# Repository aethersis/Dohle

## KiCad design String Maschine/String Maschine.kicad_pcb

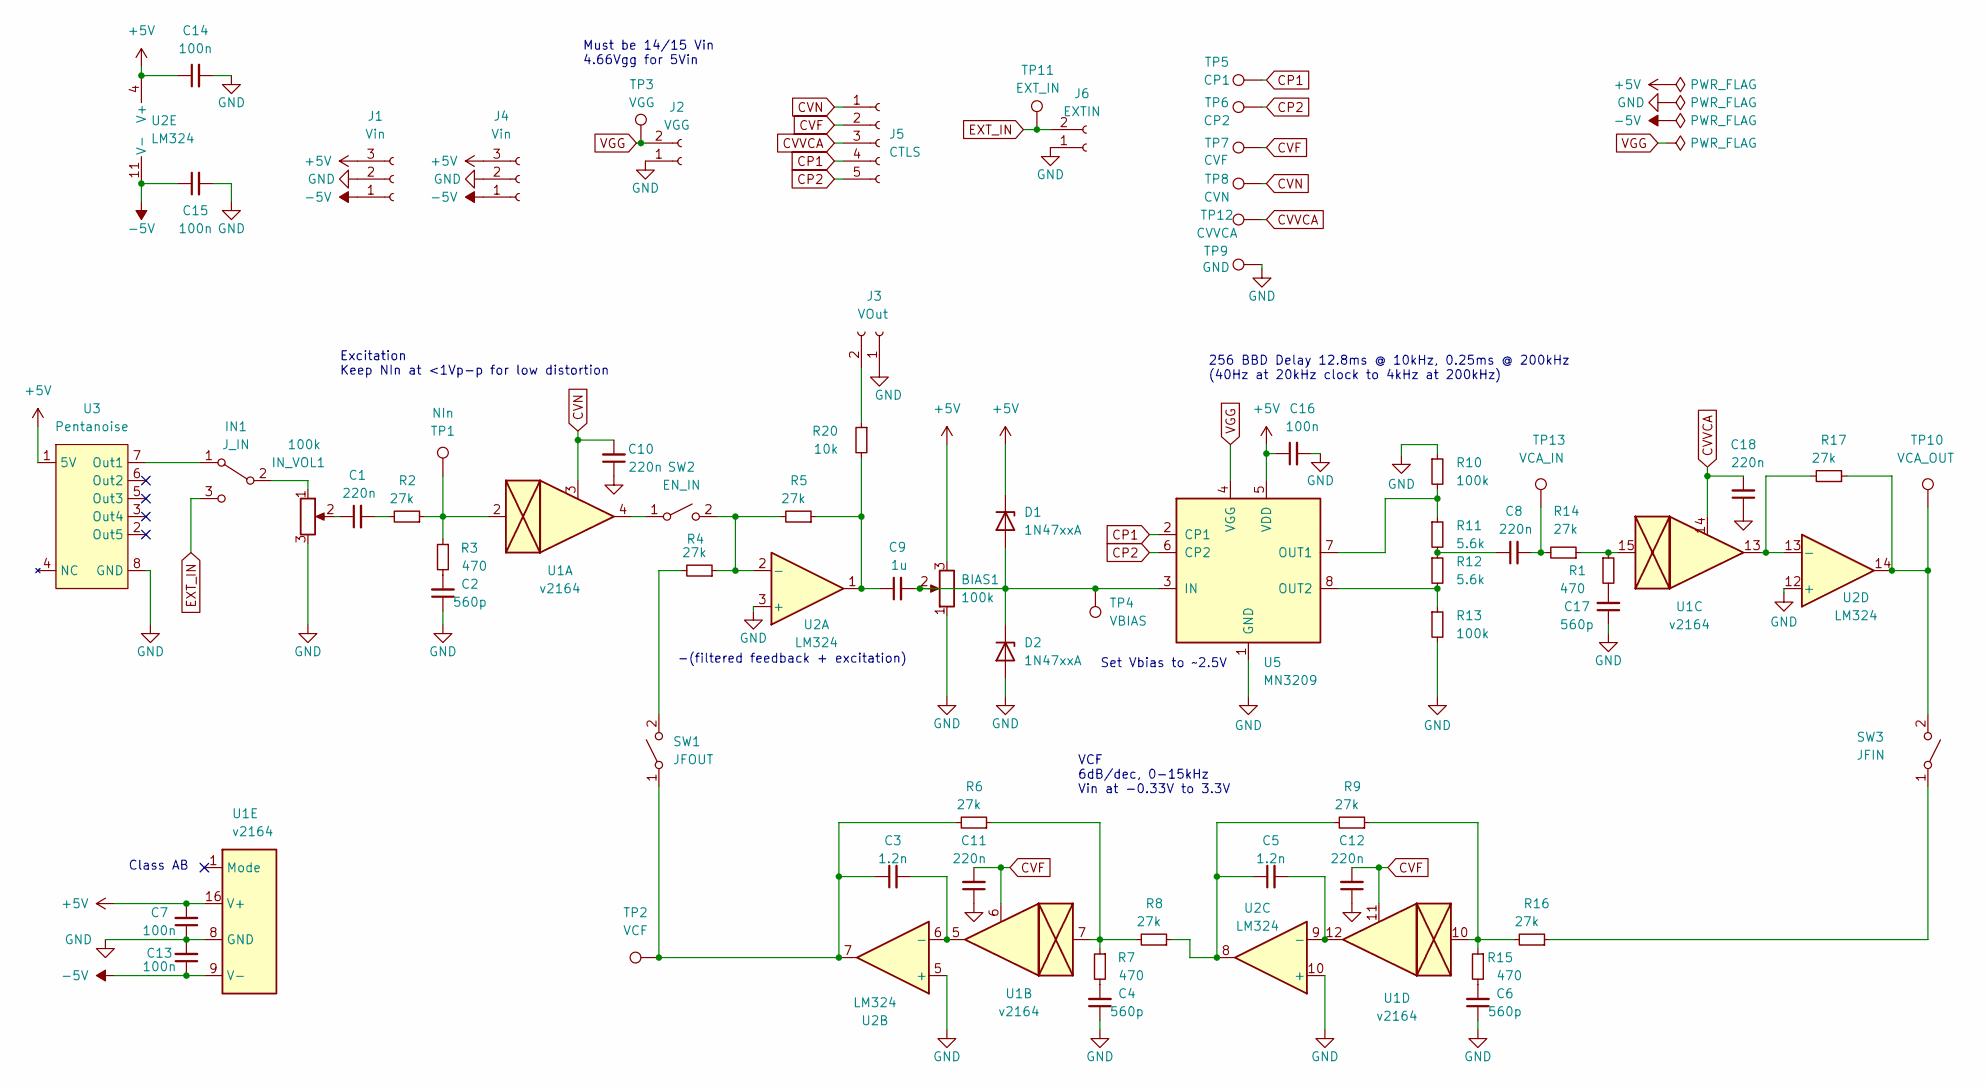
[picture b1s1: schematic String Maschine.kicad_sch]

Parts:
BIAS1: 100k; Potentiometer_Bourns_3266Y_Vertical
C1, C10, C11, C12, C18: 220n; C_Rect_L7.0mm_W3.5mm_P5.00mm
C2, C4, C6, C17: 560p; C_Disc_D5.0mm_W2.5mm_P5.00mm
C3, C5: 1.2n; C_Rect_L7.0mm_W2.5mm_P5.00mm
C7, C13, C14, C15, C16: 100n; C_Rect_L7.0mm_W3.5mm_P5.00mm
C8: 220n; C_Rect_L7.0mm_W4.5mm_P5.00mm
C9: 1u; C_Rect_L7.0mm_W4.5mm_P5.00mm
D1, D2: 1N47xxA; D_DO-41_SOD81_P7.62mm_Horizontal
IN1: J_IN; PinHeader_1x03_P2.54mm_Vertical
IN_VOL1: 100k; Potentiometer_Bourns_3266Y_Vertical
J1, J4: Vin; PinHeader_1x03_P2.54mm_Vertical
J2: VGG; PinHeader_1x02_P2.54mm_Vertical
J3: VOut; PinHeader_1x02_P2.54mm_Vertical
J5: CTLS; PinHeader_1x05_P2.54mm_Vertical
J6: EXTIN; PinHeader_1x02_P2.54mm_Vertical
R1, R3, R7, R15: 470; R_Axial_DIN0207_L6.3mm_D2.5mm_P10.16mm_Horizontal
R2, R4, R5, R6, R8, R9, R14, R16, R17: 27k; R_Axial_DIN0207_L6.3mm_D2.5mm_P10.16mm_Horizontal
R10, R13: 100k; R_Axial_DIN0207_L6.3mm_D2.5mm_P10.16mm_Horizontal
R11, R12: 5.6k; R_Axial_DIN0207_L6.3mm_D2.5mm_P10.16mm_Horizontal
R20: 10k; R_Axial_DIN0207_L6.3mm_D2.5mm_P10.16mm_Horizontal
SW1: JFOUT; PinHeader_1x02_P2.54mm_Vertical
SW2: EN_IN; PinHeader_1x02_P2.54mm_Vertical
SW3: JFIN; PinHeader_1x02_P2.54mm_Vertical
TP1: NIn; TestPoint_Pad_D1.0mm
TP2: VCF; TestPoint_Pad_D1.0mm
TP3: VGG; TestPoint_Pad_D1.0mm
TP4: VBIAS; TestPoint_Pad_D1.0mm
TP5: CP1; TestPoint_Pad_D1.0mm
TP6: CP2; TestPoint_Pad_D1.0mm
TP7: CVF; TestPoint_Pad_D1.0mm
TP8: CVN; TestPoint_Pad_D1.0mm
TP9: GND; TestPoint_Pad_D1.0mm
TP10: VCA_OUT; TestPoint_Pad_D1.0mm
TP11: EXT_IN; TestPoint_Pad_D1.0mm
TP12: CVVCA; TestPoint_Pad_D1.0mm
TP13: VCA_IN; TestPoint_Pad_D1.0mm
U1: v2164; DIP-16_W7.62mm
U2: LM324; DIP-14_W7.62mm
U3: Pentanoise; DIP-8_W7.62mm
U5: MN3209; DIP-8_W7.62mm

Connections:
+5V: BIAS1.3, C7.2, C14.1, C16.1, D1.1 (K), J1.3, J4.3, U1.16 (V+), U2.4 (V+), U3.1 (5V), U5.5 (VDD)
-5V: C13.1, C15.1, J1.1, J4.1, U1.9 (V-), U2.11 (V-)
CP1: J5.4, TP5.1, U5.2 (CP1)
CP2: J5.5, TP6.1, U5.6 (CP2)
CVF: C11.2, C12.2, J5.2, TP7.1, U1.6, U1.11
CVN: C10.2, J5.1, TP8.1, U1.3
CVVCA: C18.2, J5.3, TP12.1, U1.14
EXT_IN: IN1.3 (C), J6.2, TP11.1
GND: BIAS1.1, C2.1, C4.1, C6.1, C7.1, C10.1, C11.1, C12.1, C13.2, C14.2, C15.2, C16.2, C17.1, C18.1, D2.2 (A), IN_VOL1.3, J1.2, J2.1, J3.1, J4.2, J6.1, R10.1, R13.2, TP9.1, U1.8 (GND), U2.3 (+), U2.5 (+), U2.10 (+), U2.12 (+), U3.8 (GND), U5.1 (GND)
unnamed: BIAS1.2, C9.2, D1.2 (A), D2.1 (K), TP4.1, U5.3 (IN)
unnamed: C1.1, IN_VOL1.2
unnamed: C1.2, R2.2
unnamed: C2.2, R3.2
unnamed: C3.1, R6.2, SW1.1 (A), TP2.1, U2.7
unnamed: C3.2, U1.5, U2.6 (-)
unnamed: C4.2, R7.2
unnamed: C5.1, R8.1, R9.2, U2.8
unnamed: C5.2, U1.12, U2.9 (-)
unnamed: C6.2, R15.2
unnamed: C8.1, R11.2, R12.1
unnamed: C8.2, R14.2, TP13.1
unnamed: C9.1, R5.1, R20.2, U2.1
unnamed: C17.2, R1.2
unnamed: IN1.1 (A), U3.7 (Out1)
unnamed: IN1.2 (B), IN_VOL1.1
unnamed: J3.2, R20.1
unnamed: R1.1, R14.1, U1.15
unnamed: R2.1, R3.1, TP1.1, U1.2
unnamed: R4.1, R5.2, SW2.2 (B), U2.2 (-)
unnamed: R4.2, SW1.2 (B)
unnamed: R6.1, R7.1, R8.2, U1.7
unnamed: R10.2, R11.1, U5.7 (OUT1)
unnamed: R12.2, R13.1, U5.8 (OUT2)
unnamed: R9.1, R15.1, R16.2, U1.10
unnamed: R16.1, SW3.1 (A)
unnamed: R17.1, SW3.2 (B), TP10.1, U2.14
unnamed: R17.2, U1.13, U2.13 (-)
unnamed: SW2.1 (A), U1.4
VGG: J2.2, TP3.1, U5.4 (VGG)

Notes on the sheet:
Must be 14/15 Vin 4.66Vgg for 5Vin
Set Vbias to ~2.5V
Excitation Keep NIn at <1Vp-p for low distortion
256 BBD Delay 12.8ms @ 10kHz, 0.25ms @ 200kHz (40Hz at 20kHz clock to 4kHz at 200kHz)
VCF 6dB/dec, 0-15kHz Vin at -0.33V to 3.3V
-(filtered feedback + excitation)
Class AB

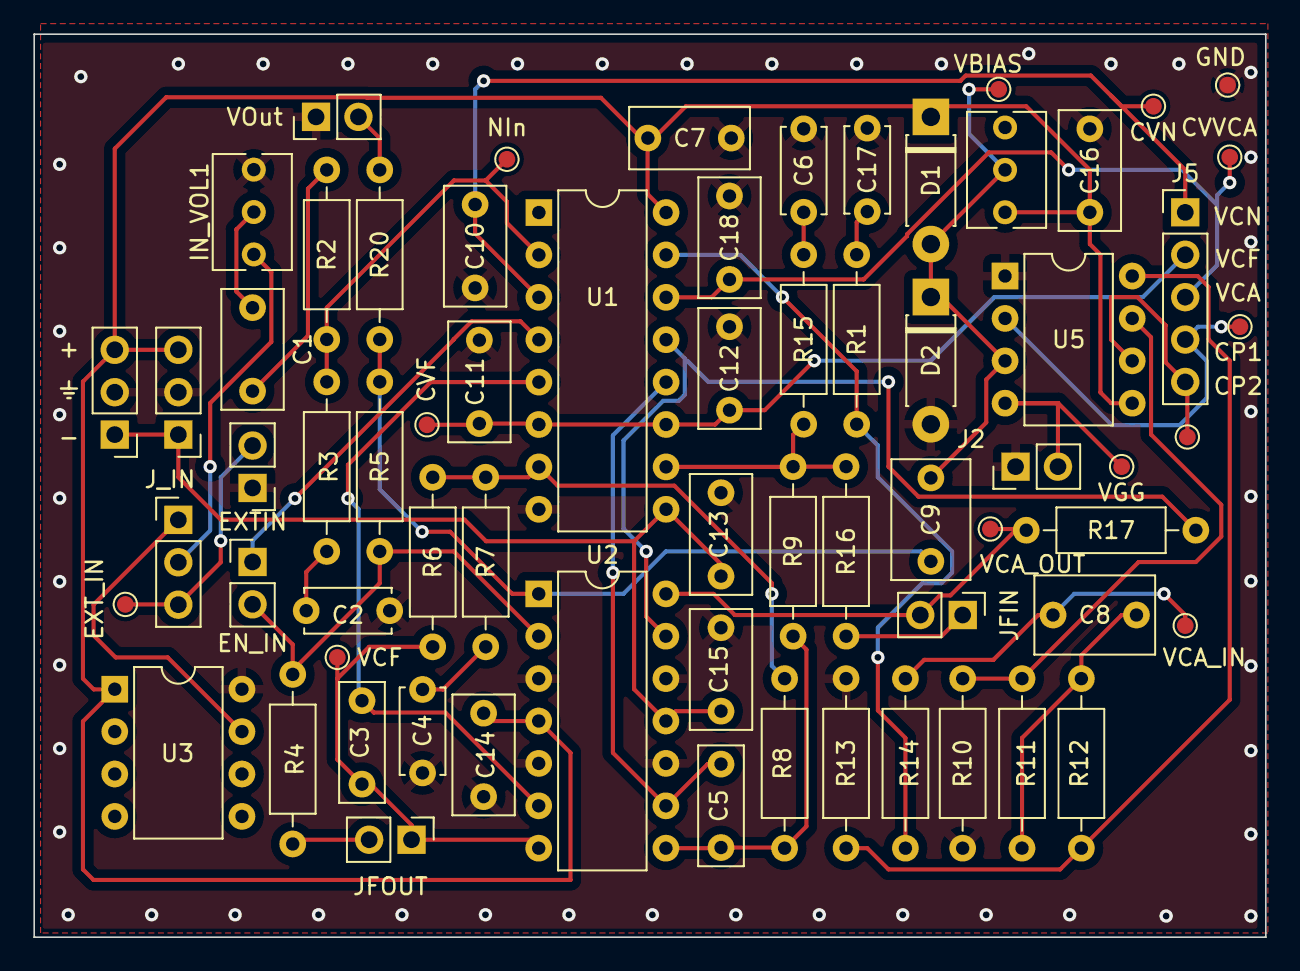
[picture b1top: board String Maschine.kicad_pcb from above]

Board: 2 copper layers, 73.8 x 54.1 mm, 67 parts (0 on the bottom side), 39 nets.

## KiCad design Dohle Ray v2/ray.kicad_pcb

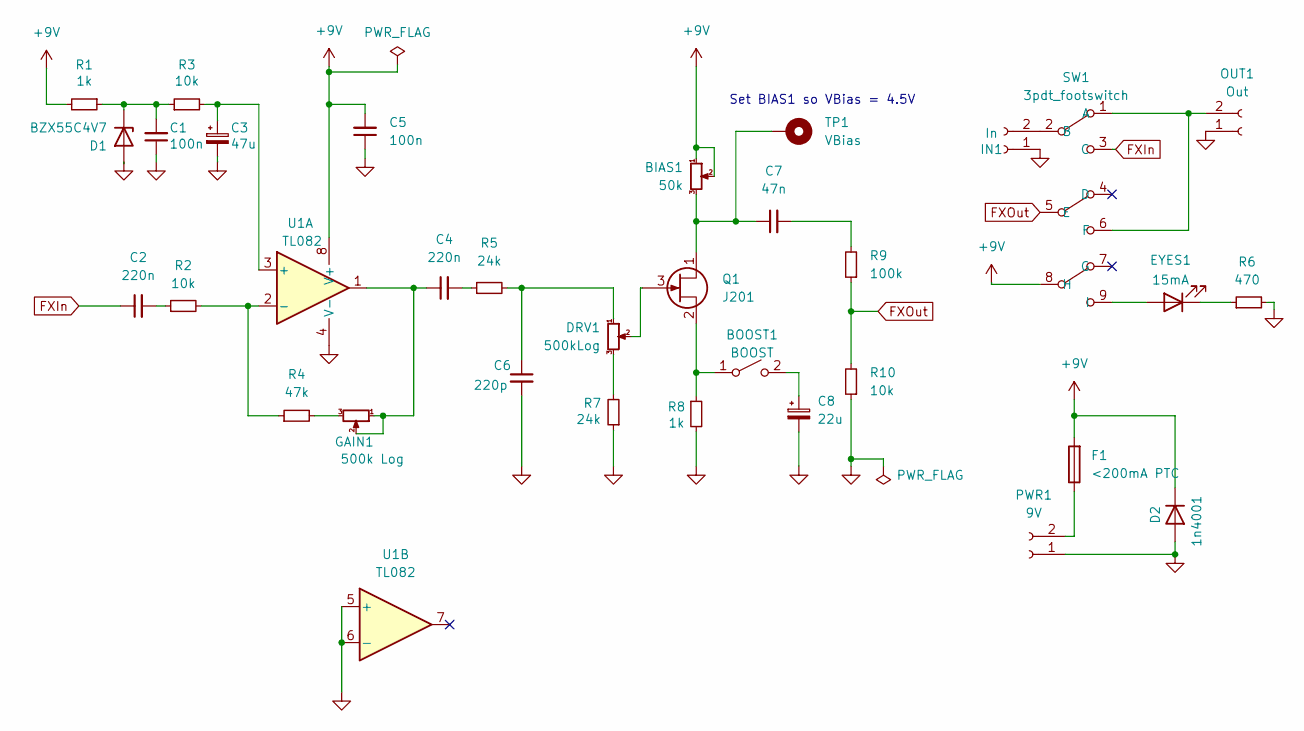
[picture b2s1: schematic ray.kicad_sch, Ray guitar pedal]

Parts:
BIAS1: 50k; Potentiometer_Bourns_3299W_Vertical
BOOST1: BOOST; JST_PH_B2B-PH-K_1x02_P2.00mm_Vertical
C1, C5: 100n; C_Rect_L7.0mm_W4.5mm_P5.00mm
C2, C4: 220n; C_Rect_L7.0mm_W4.5mm_P5.00mm
C3: 47u; CP_Radial_D5.0mm_P2.00mm
C6: 220p; C_Rect_L7.0mm_W2.0mm_P5.00mm
C7: 47n; C_Disc_D5.0mm_W2.5mm_P5.00mm
C8: 22u; CP_Radial_D5.0mm_P2.50mm
D1: BZX55C4V7; D_DO-35_SOD27_P7.62mm_Horizontal
D2: 1n4001; D_DO-15_P12.70mm_Horizontal
DRV1: 500kLog; JST_PH_B3B-PH-K_1x03_P2.00mm_Vertical
EYES1: 15mA; JST_PH_B2B-PH-K_1x02_P2.00mm_Vertical
F1: <200mA PTC; C_Rect_L7.0mm_W4.5mm_P5.00mm
GAIN1: 500k Log; JST_PH_B3B-PH-K_1x03_P2.00mm_Vertical
IN1: In; JST_PH_B2B-PH-K_1x02_P2.00mm_Vertical
OUT1: Out; JST_PH_B2B-PH-K_1x02_P2.00mm_Vertical
PWR1: 9V; JST_PH_B2B-PH-K_1x02_P2.00mm_Vertical
Q1: J201; SOT-23_Handsoldering
R1, R8: 1k; R_Axial_DIN0207_L6.3mm_D2.5mm_P10.16mm_Horizontal
R2, R3, R10: 10k; R_Axial_DIN0207_L6.3mm_D2.5mm_P10.16mm_Horizontal
R4: 47k; R_Axial_DIN0207_L6.3mm_D2.5mm_P10.16mm_Horizontal
R5, R7: 24k; R_Axial_DIN0207_L6.3mm_D2.5mm_P10.16mm_Horizontal
R6: 470; R_Axial_DIN0207_L6.3mm_D2.5mm_P10.16mm_Horizontal
R9: 100k; R_Axial_DIN0207_L6.3mm_D2.5mm_P10.16mm_Horizontal
SW1: 3pdt_footswitch
TP1: VBias; TestPoint_THTPad_1.5x1.5mm_Drill0.7mm
U1: TL082; DIP-8_W7.62mm_Socket_LongPads

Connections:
+9V: BIAS1.1, BIAS1.2, C5.2, D2.1 (K), F1.2, R1.2, SW1.8 (H), U1.8 (V+)
FXIn: C2.1, SW1.3 (C)
FXOut: R9.1, R10.2, SW1.5 (E)
GND: C1.1, C3.2, C5.1, C6.2, C8.2, D1.2 (A), D2.2 (A), IN1.1, OUT1.1, PWR1.1, R6.2, R7.1, R8.2, R10.1, U1.4 (V-), U1.5 (+), U1.6 (-)
unnamed 4: BIAS1.3, C7.1, Q1.1 (D), TP1.1; also elsewhere on the board
unnamed: BOOST1.1 (A), Q1.2 (S), R8.1
unnamed: BOOST1.2 (B), C8.1
unnamed: C1.2, D1.1 (K), R1.1, R3.1
unnamed: C2.2, R2.1
unnamed: C3.1, R3.2, U1.3 (+)
unnamed: C4.1, GAIN1.1, GAIN1.2, U1.1
unnamed: C4.2, R5.1
unnamed: C6.1, DRV1.1, R5.2
unnamed: C7.2, R9.2
unnamed: DRV1.2, Q1.3 (G)
unnamed: DRV1.3, R7.2
unnamed: EYES1.1 (K), R6.1
unnamed: EYES1.2 (A), SW1.9 (I)
unnamed: F1.1, PWR1.2
unnamed: GAIN1.3, R4.2
unnamed: IN1.2, SW1.2 (B)
unnamed: OUT1.2, SW1.1 (A), SW1.6 (F)
unnamed: R2.2, R4.1, U1.2 (-)

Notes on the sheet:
Set BIAS1 so VBias = 4.5V

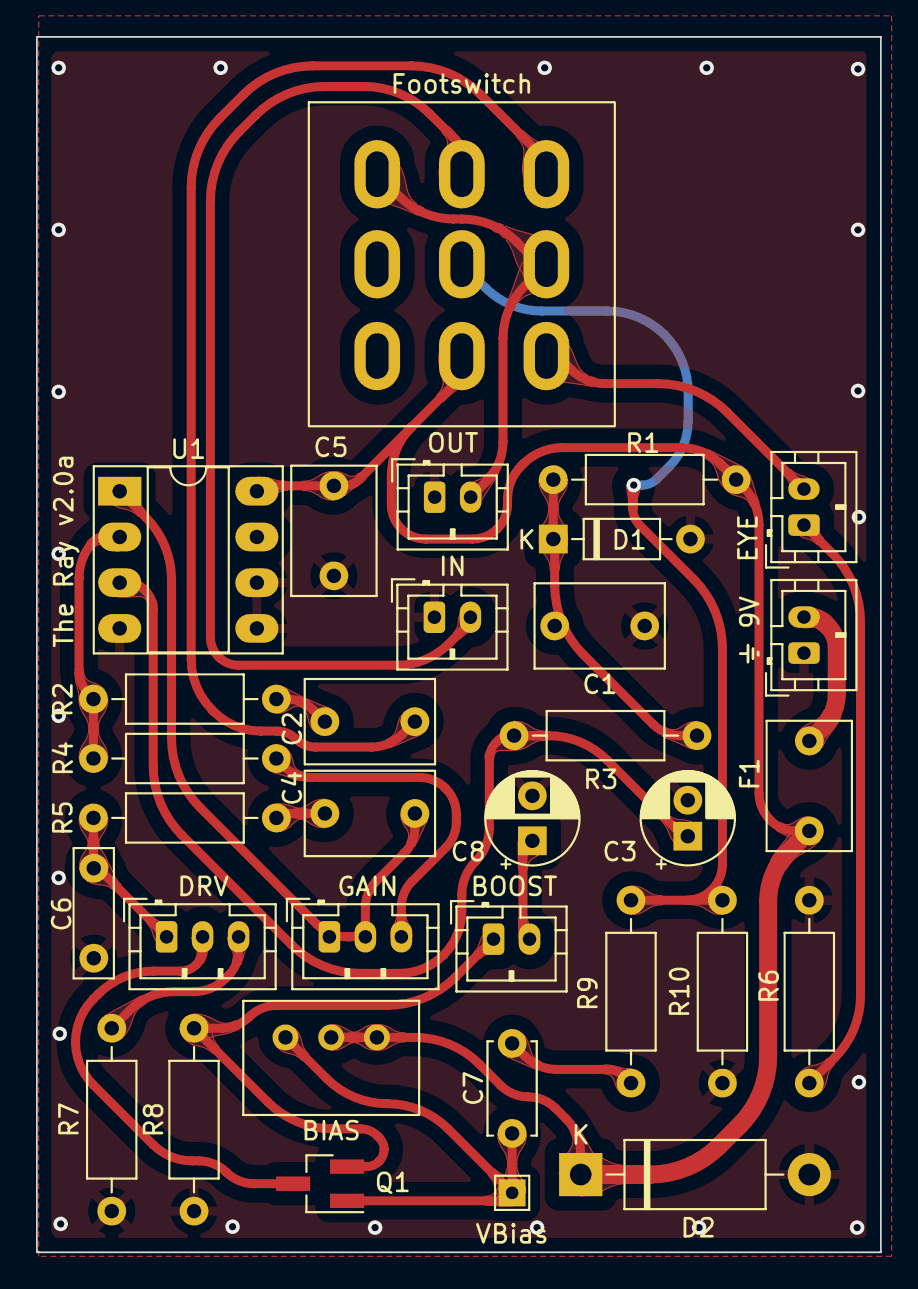
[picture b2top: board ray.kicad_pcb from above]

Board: 2 copper layers, 46.9 x 67.5 mm, 33 parts (0 on the bottom side), 23 nets.

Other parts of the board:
VBias: VBias; TestPoint_THTPad_1.5x1.5mm_Drill0.7mm

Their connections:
unnamed 4: VBias.1; also elsewhere on the board

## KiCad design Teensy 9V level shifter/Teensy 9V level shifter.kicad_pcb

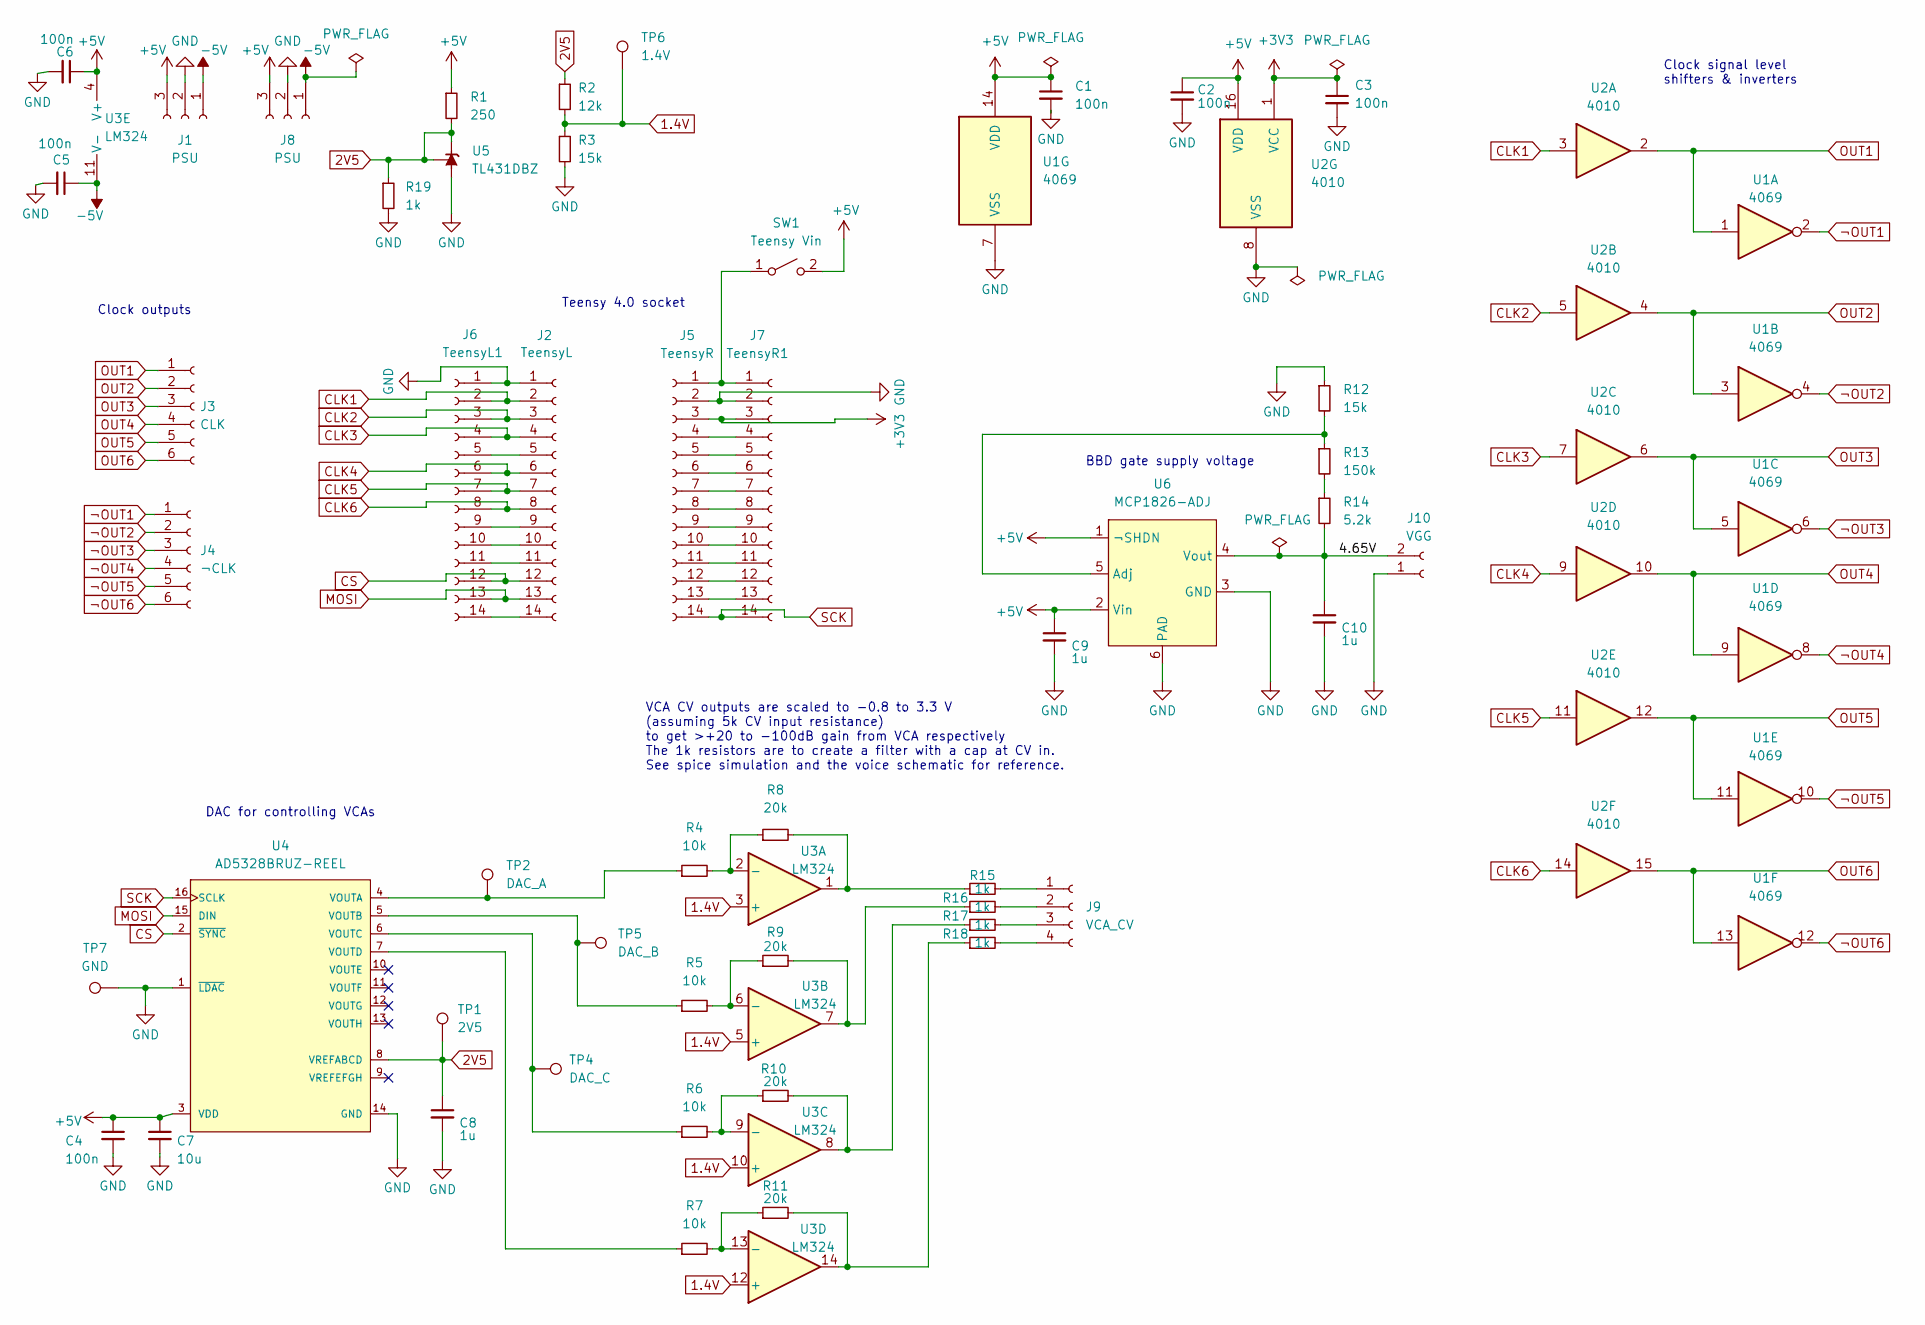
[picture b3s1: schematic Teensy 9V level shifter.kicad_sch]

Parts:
C1, C2, C3: 100n; C_Rect_L7.0mm_W3.5mm_P5.00mm
C4, C5, C6: 100n; C_0603_1608Metric_Pad1.08x0.95mm_HandSolder
C7: 10u; C_0805_2012Metric_Pad1.18x1.45mm_HandSolder
C8, C9, C10: 1u; C_0603_1608Metric_Pad1.08x0.95mm_HandSolder
J1, J8: PSU; PinHeader_1x03_P2.54mm_Vertical
J2: TeensyL; PinHeader_1x14_P2.54mm_Vertical
J3: CLK; PinHeader_1x06_P2.54mm_Vertical
J4: ¬CLK; PinHeader_1x06_P2.54mm_Vertical
J5: TeensyR; PinHeader_1x14_P2.54mm_Vertical
J6: TeensyL1; PinHeader_1x14_P2.54mm_Vertical
J7: TeensyR1; PinHeader_1x14_P2.54mm_Vertical
J9: VCA_CV; PinHeader_1x04_P2.54mm_Vertical
J10: VGG; PinHeader_1x02_P2.54mm_Vertical
R1: 250; R_0603_1608Metric_Pad0.98x0.95mm_HandSolder
R2: 12k; R_0603_1608Metric_Pad0.98x0.95mm_HandSolder
R3, R12: 15k; R_0603_1608Metric_Pad0.98x0.95mm_HandSolder
R4, R5, R6, R7: 10k; R_0603_1608Metric_Pad0.98x0.95mm_HandSolder
R8, R9, R10, R11: 20k; R_0603_1608Metric_Pad0.98x0.95mm_HandSolder
R13: 150k; R_0603_1608Metric_Pad0.98x0.95mm_HandSolder
R14: 5.2k; R_0603_1608Metric_Pad0.98x0.95mm_HandSolder
R15, R16, R17, R18, R19: 1k; R_0603_1608Metric_Pad0.98x0.95mm_HandSolder
SW1: Teensy Vin; PinHeader_1x02_P2.54mm_Vertical
TP1: 2V5; TestPoint_Pad_D1.0mm
TP2: DAC_A; TestPoint_Pad_D1.0mm
TP4: DAC_C; TestPoint_Pad_D1.0mm
TP5: DAC_B; TestPoint_Pad_D1.0mm
TP6: 1.4V; TestPoint_Pad_D1.0mm
TP7: GND; TestPoint_Pad_3.0x3.0mm
U1: 4069; DIP-14_W7.62mm
U2: 4010; DIP-16_W7.62mm
U3: LM324; SO-14_3.9x8.65mm_P1.27mm
U4: AD5328BRUZ-REEL; TSSOP-16_4.4x5mm_P0.65mm
U5: TL431DBZ; SOT-23
U6: MCP1826-ADJ; SOT-223-6

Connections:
1.4V: R2.2, R3.1, TP6.1, U3.3 (+), U3.5 (+), U3.10 (+), U3.12 (+)
2V5: C8.1, R1.2, R2.1, R19.1, TP1.1, U4.8 (VREFABCD), U5.1 (K), U5.2 (REF)
+3V3: C3.1, J5.3, J7.3, U2.1 (VCC)
+5V: C1.1, C2.1, C4.1, C6.1, C7.1, C9.1, J1.3, J8.3, R1.1, SW1.2 (B), U1.14 (VDD), U2.16 (VDD), U3.4 (V+), U4.3 (VDD), U6.1 (¬SHDN), U6.2 (Vin)
-5V: C5.1, J1.1, J8.1, U3.11 (V-)
/4.65V: C10.1, J10.2, R14.2, U6.4 (Vout)
CLK1: J2.2, J6.2, U2.3
CLK2: J2.3, J6.3, U2.5
CLK3: J2.4, J6.4, U2.7
CLK4: J2.6, J6.6, U2.9
CLK5: J2.7, J6.7, U2.11
CLK6: J2.8, J6.8, U2.14
CS: J2.12, J6.12, U4.2 (~SYNC)
GND: C1.2, C2.2, C3.2, C4.2, C5.2, C6.2, C7.2, C8.2, C9.2, C10.2, J1.2, J2.1, J5.2, J6.1, J7.2, J8.2, J10.1, R3.2, R12.1, R19.2, TP7.1, U1.7 (VSS), U2.8 (VSS), U4.1 (~LDAC), U4.14 (GND), U5.3 (A), U6.3 (GND), U6.6 (PAD)
MOSI: J2.13, J6.13, U4.15 (DIN)
unnamed: J2.5, J6.5
unnamed: J2.9, J6.9
unnamed: J2.10, J6.10
unnamed: J2.11, J6.11
unnamed: J2.14, J6.14
unnamed: J5.1, J7.1, SW1.1 (A)
unnamed: J5.4, J7.4
unnamed: J5.5, J7.5
unnamed: J5.6, J7.6
unnamed: J5.7, J7.7
unnamed: J5.8, J7.8
unnamed: J5.9, J7.9
unnamed: J5.10, J7.10
unnamed: J5.11, J7.11
unnamed: J5.12, J7.12
unnamed: J5.13, J7.13
unnamed: J9.1, R15.2
unnamed: J9.2, R16.2
unnamed: J9.3, R17.2
unnamed: J9.4, R18.2
unnamed: R4.1, TP2.1, U4.4 (VOUTA)
unnamed: R5.1, TP5.1, U4.5 (VOUTB)
unnamed: R5.2, R9.1, U3.6 (-)
unnamed: R7.1, U4.7 (VOUTD)
unnamed: R8.2, R15.1, U3.1
unnamed: R6.2, R10.1, U3.9 (-)
unnamed: R10.2, R17.1, U3.8
unnamed: R7.2, R11.1, U3.13 (-)
unnamed: R12.2, R13.1, U6.5 (Adj)
unnamed: R13.2, R14.1
unnamed: R6.1, TP4.1, U4.6 (VOUTC)
unnamed: R4.2, R8.1, U3.2 (-)
unnamed: R9.2, R16.1, U3.7
unnamed: R11.2, R18.1, U3.14
OUT1: J3.1, U1.1, U2.2
OUT2: J3.2, U1.3, U2.4
OUT3: J3.3, U1.5, U2.6
OUT4: J3.4, U1.9, U2.10
OUT5: J3.5, U1.11, U2.12
OUT6: J3.6, U1.13, U2.15
SCK: J5.14, J7.14, U4.16 (SCLK)
¬OUT1: J4.1, U1.2
¬OUT2: J4.2, U1.4
¬OUT3: J4.3, U1.6
¬OUT4: J4.4, U1.8
¬OUT5: J4.5, U1.10
¬OUT6: J4.6, U1.12

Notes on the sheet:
Clock outputs
BBD gate supply voltage
Clock signal level shifters & inverters
DAC for controlling VCAs
VCA CV outputs are scaled to -0.8 to 3.3 V (assuming 5k CV input resistance) to get >+20 to -100dB gain from VCA respectively The 1k resistors are to create a filter with a cap at CV in. See spice simulation and the voice schematic for reference.
Teensy 4.0 socket

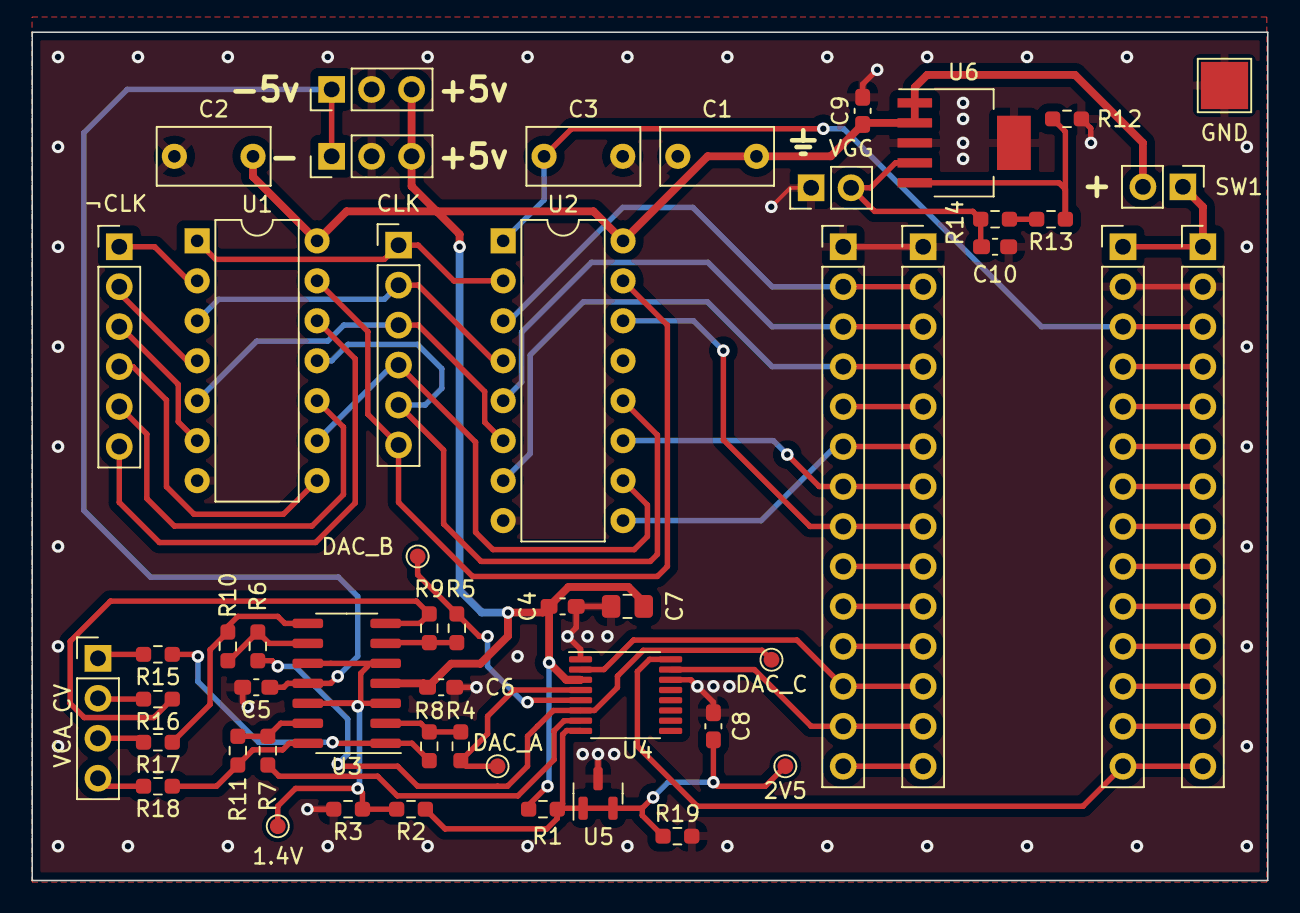
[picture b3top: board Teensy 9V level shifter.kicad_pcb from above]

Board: 2 copper layers, 78.5 x 53.9 mm, 52 parts (0 on the bottom side), 62 nets.

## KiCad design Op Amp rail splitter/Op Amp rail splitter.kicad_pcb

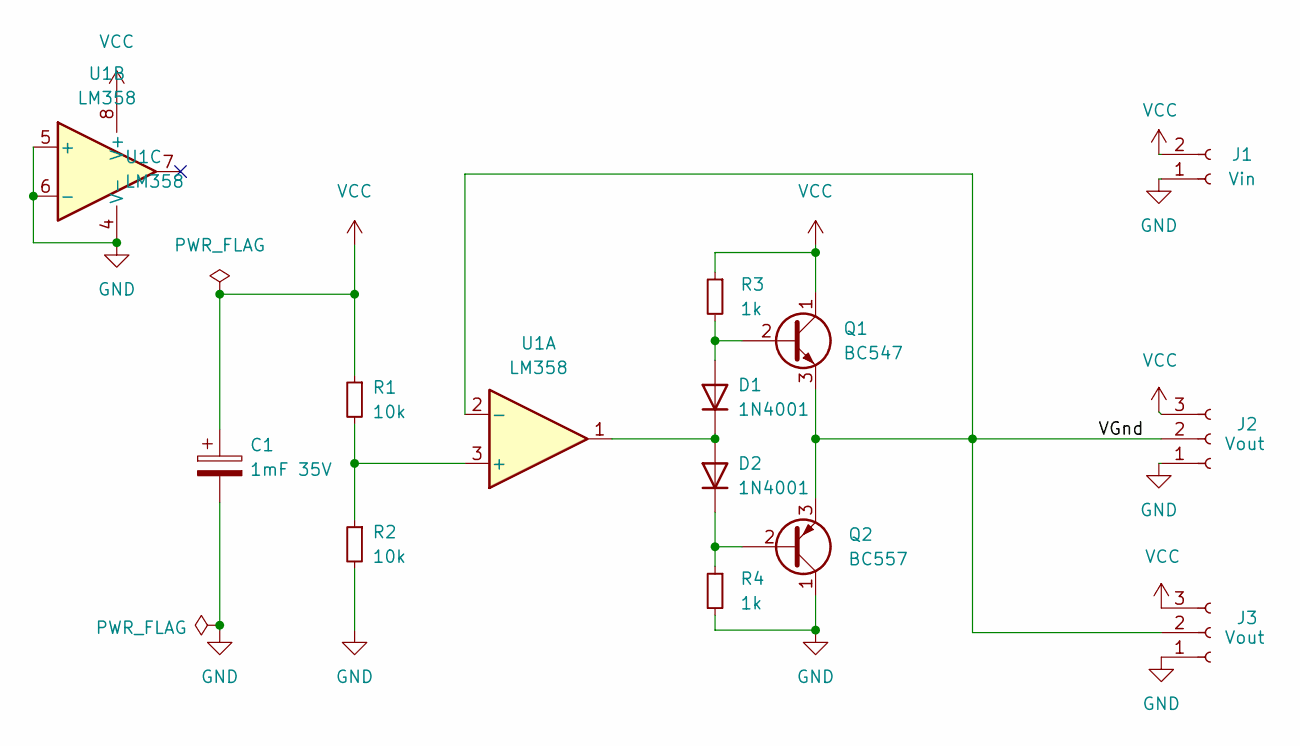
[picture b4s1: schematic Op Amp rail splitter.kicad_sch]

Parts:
C1: 1mF 35V; CP_Radial_D12.5mm_P5.00mm
D1, D2: 1N4001; D_DO-41_SOD81_P10.16mm_Horizontal
J1: Vin; PinHeader_1x02_P2.54mm_Vertical
J2, J3: Vout; PinHeader_1x03_P2.54mm_Vertical
Q1: BC547; TO-92_Inline
Q2: BC557; TO-92_Inline
R1, R2: 10k; R_Axial_DIN0207_L6.3mm_D2.5mm_P10.16mm_Horizontal
R3, R4: 1k; R_Axial_DIN0207_L6.3mm_D2.5mm_P10.16mm_Horizontal
U1: LM358; DIP-8_W7.62mm

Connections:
/VGnd: J2.2, J3.2, Q1.3 (E), Q2.3 (E), U1.2 (-)
GND: C1.2, J1.1, J2.1, J3.1, Q2.1 (C), R2.2, R4.2, U1.4 (V-), U1.5 (+), U1.6 (-)
unnamed: D1.1 (K), D2.2 (A), U1.1
unnamed: D1.2 (A), Q1.2 (B), R3.2
unnamed: D2.1 (K), Q2.2 (B), R4.1
unnamed: R1.2, R2.1, U1.3 (+)
VCC: C1.1, J1.2, J2.3, J3.3, Q1.1 (C), R1.1, R3.1, U1.8 (V+)

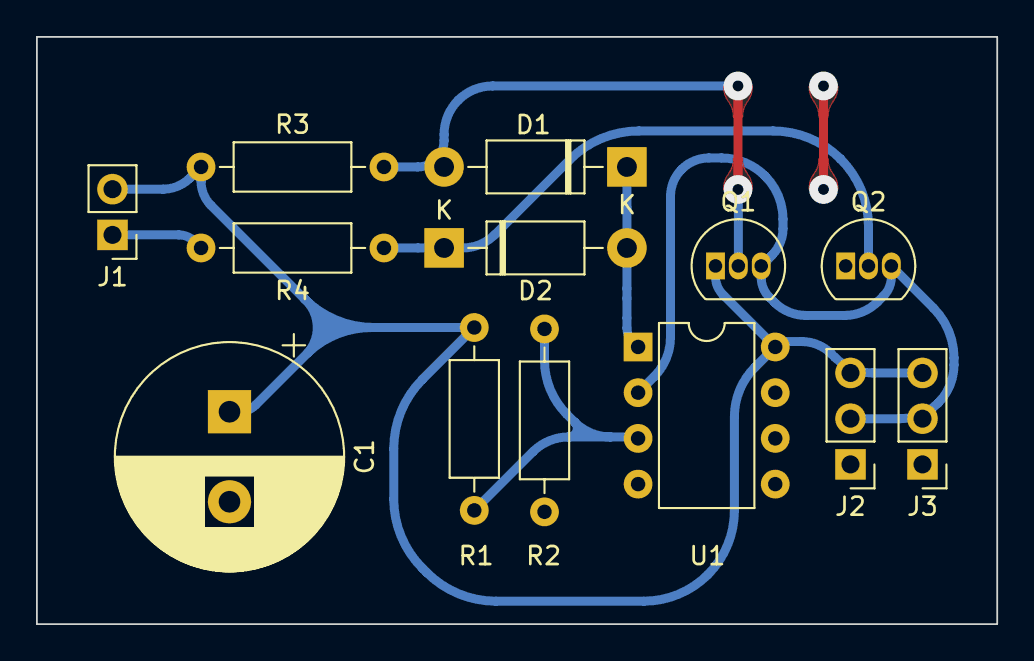
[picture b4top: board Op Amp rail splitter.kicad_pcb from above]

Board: 2 copper layers, 53.4 x 32.6 mm, 13 parts (0 on the bottom side), 7 nets.

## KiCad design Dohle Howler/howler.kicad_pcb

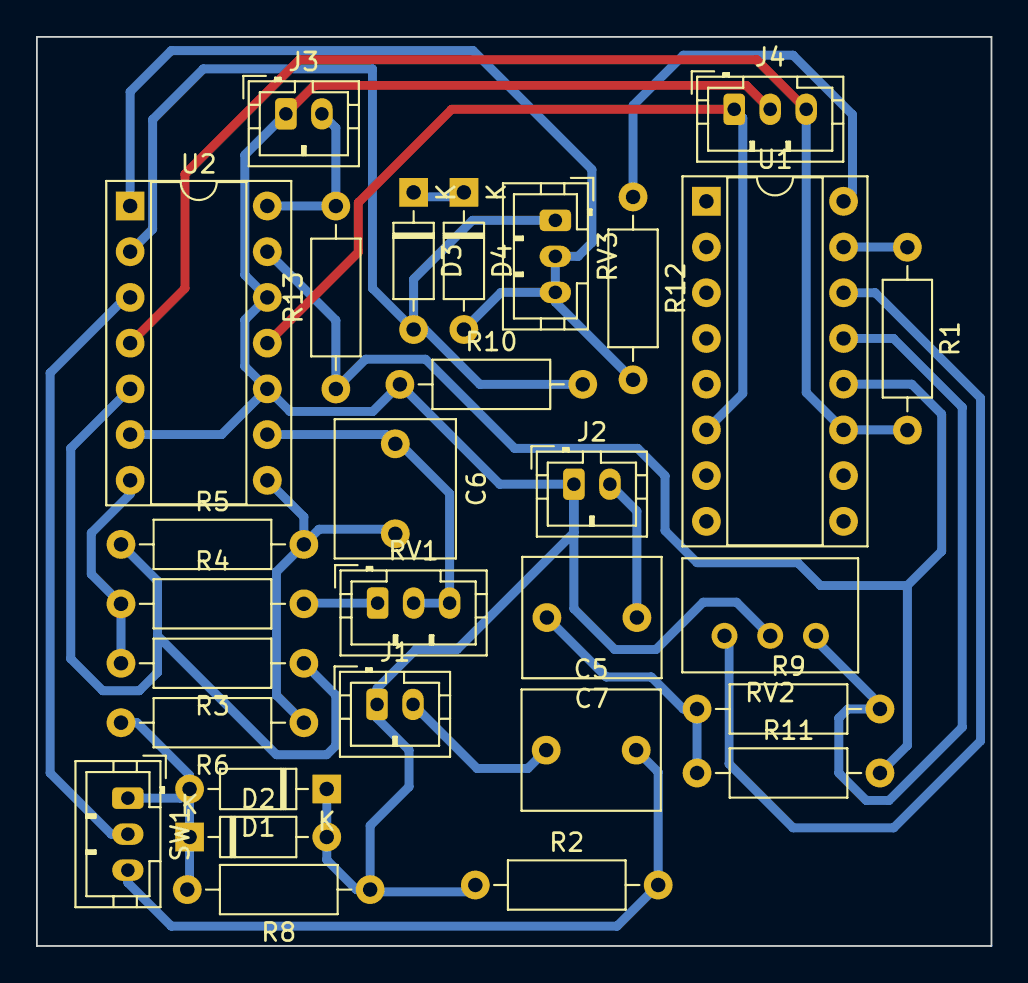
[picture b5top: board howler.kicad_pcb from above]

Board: 2 copper layers, 53.0 x 50.5 mm, 29 parts (0 on the bottom side), 23 nets.

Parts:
C5, C6, C7: 1u; C_Rect_L7.5mm_W6.5mm_P5.00mm
D1, D2: 1n4148; D_DO-35_SOD27_P7.62mm_Horizontal
D3, D4: 4v7; D_DO-35_SOD27_P7.62mm_Horizontal
J1: MOD_IN; JST_PH_B2B-PH-K_1x02_P2.00mm_Vertical
J2: IN; JST_PH_B2B-PH-K_1x02_P2.00mm_Vertical
J3: OUT; JST_PH_B2B-PH-K_1x02_P2.00mm_Vertical
J4: PWR; JST_PH_B3B-PH-K_1x03_P2.00mm_Vertical
R1, R3, R4, R5, R8, R9, R11: 10k; R_Axial_DIN0207_L6.3mm_D2.5mm_P10.16mm_Horizontal
R2: 470k; R_Axial_DIN0207_L6.3mm_D2.5mm_P10.16mm_Horizontal
R6: 100k; R_Axial_DIN0207_L6.3mm_D2.5mm_P10.16mm_Horizontal
R10: 4k7; R_Axial_DIN0207_L6.3mm_D2.5mm_P10.16mm_Horizontal
R12: 15k; R_Axial_DIN0207_L6.3mm_D2.5mm_P10.16mm_Horizontal
R13: 24k; R_Axial_DIN0207_L6.3mm_D2.5mm_P10.16mm_Horizontal
RV1: 500k log; JST_PH_B3B-PH-K_1x03_P2.00mm_Vertical
RV2: 2k; Potentiometer_Bourns_3299W_Vertical
RV3: 50k; JST_PH_B3B-PH-K_1x03_P2.00mm_Vertical
SW1: SW_SPDT; JST_PH_B3B-PH-K_1x03_P2.00mm_Vertical
U1: LM13700; DIP-16_W7.62mm_Socket
U2: LM324; DIP-14_W7.62mm_Socket

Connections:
+9V: J4.3, R1.2, U1.11 (V+), U2.4 (V+)
-9V: J4.1, U1.6 (V-), U2.11 (V-)
D_BIAS: R1.1, U1.15 (DIODE_BIAS)
EXT_MOD: C5.2, R2.2, SW1.3 (C)
GND: D1.1 (K), D2.2 (A), J1.1, J2.1, J3.1, J4.2, R2.1, R8.1, R10.1, RV2.2, U2.6 (-), U2.10 (+), U2.12 (+)
unnamed: C5.1, J1.2
unnamed: C6.1, RV1.2, RV1.3, U2.9 (-)
unnamed: C6.2, R5.2, R6.1, U2.8
unnamed: C7.1, J2.2
unnamed: C7.2, R9.1, R11.1
unnamed: D1.2 (A), D2.1 (K), R6.2, R8.2, SW1.1 (A)
unnamed: D3.1 (K), D4.1 (K)
unnamed: D3.2 (A), R10.2, RV3.1, U2.2 (-)
unnamed: D4.2 (A), R12.2, RV3.2, RV3.3, U2.1
unnamed: J3.2, R13.2, U2.14
unnamed: R3.1, R5.1, U2.5 (+)
unnamed: R3.2, R4.1, U2.7
unnamed: R4.2, RV1.1
unnamed: R9.2, RV2.3, U1.13 (-)
unnamed: R11.2, R13.1, U1.12, U2.13 (-)
unnamed: R12.1, U1.16
unnamed: RV2.1, U1.14 (+)
unnamed: SW1.2 (B), U2.3 (+)

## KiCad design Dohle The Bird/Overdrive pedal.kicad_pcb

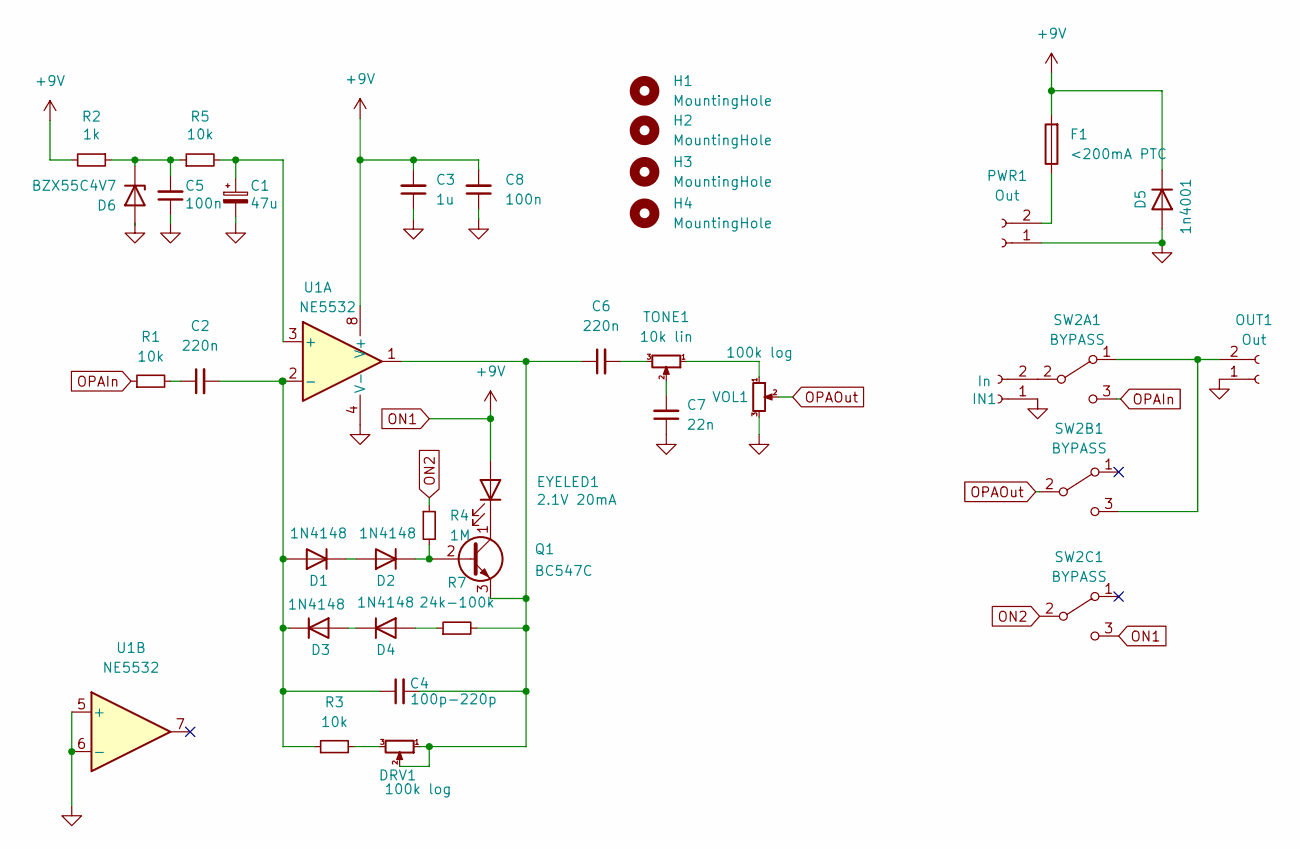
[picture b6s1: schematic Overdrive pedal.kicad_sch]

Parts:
C1: 47u; CP_Radial_D5.0mm_P2.00mm
C2, C6: 220n; C_Rect_L7.0mm_W4.5mm_P5.00mm
C3: 1u; C_Rect_L7.5mm_W6.5mm_P5.00mm
C4: 100p-220p; C_Rect_L7.0mm_W3.5mm_P5.00mm
C5, C8: 100n; C_Rect_L7.0mm_W4.5mm_P5.00mm
C7: 22n; C_Disc_D3.0mm_W1.6mm_P2.50mm
D1, D2, D3, D4: 1N4148; D_DO-35_SOD27_P7.62mm_Horizontal
D5: 1n4001; D_DO-15_P12.70mm_Horizontal
D6: BZX55C4V7; D_DO-35_SOD27_P7.62mm_Horizontal
DRV1: 100k log; JST_PH_B3B-PH-K_1x03_P2.00mm_Vertical
EYELED1: 2.1V 20mA; JST_PH_B2B-PH-K_1x02_P2.00mm_Vertical
F1: <200mA PTC; C_Rect_L7.0mm_W4.5mm_P5.00mm
H1, H2, H3, H4: MountingHole; MountingHole_3.2mm_M3
IN1: In; JST_PH_B2B-PH-K_1x02_P2.00mm_Vertical
OUT1: Out; JST_PH_B2B-PH-K_1x02_P2.00mm_Vertical
PWR1: Out; JST_PH_B2B-PH-K_1x02_P2.00mm_Vertical
Q1: BC547C; TO-92_Inline_Wide
R1, R3, R5: 10k; R_Axial_DIN0207_L6.3mm_D2.5mm_P10.16mm_Horizontal
R2: 1k; R_Axial_DIN0207_L6.3mm_D2.5mm_P10.16mm_Horizontal
R4: 1M; R_Axial_DIN0207_L6.3mm_D2.5mm_P10.16mm_Horizontal
R7: 24k-100k; R_Axial_DIN0207_L6.3mm_D2.5mm_P10.16mm_Horizontal
SW2A1, SW2B1, SW2C1: BYPASS; JST_PH_B3B-PH-K_1x03_P2.00mm_Vertical
TONE1: 10k lin; JST_PH_B3B-PH-K_1x03_P2.00mm_Vertical
U1: NE5532; DIP-8_W7.62mm_Socket
VOL1: 100k log; JST_PH_B3B-PH-K_1x03_P2.00mm_Vertical

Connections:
GND: C1.2, C3.1, C5.1, C7.1, C8.1, D5.2 (A), D6.2 (A), IN1.1, OUT1.1, PWR1.1, U1.4 (V-), U1.5 (+), U1.6 (-), VOL1.3
unnamed: C1.1, R5.2, U1.3 (+)
unnamed: C2.1, R1.2
unnamed: C2.2, C4.1, D1.1 (K), D3.2 (A), R3.1, U1.2 (-)
unnamed: C4.2, C6.1, DRV1.1, DRV1.2, Q1.3 (E), R7.2, U1.1
unnamed: C5.2, D6.1 (K), R2.1, R5.1
unnamed: C6.2, TONE1.3
unnamed: C7.2, TONE1.2
unnamed: D1.2 (A), D4.1 (K)
unnamed: D2.1 (K), Q1.2 (B), R4.2
unnamed: D2.2 (A), D3.1 (K)
unnamed: D4.2 (A), R7.1
unnamed: DRV1.3, R3.2
unnamed: EYELED1.1 (K), Q1.1 (C)
unnamed: F1.1, PWR1.2
unnamed: IN1.2, SW2A1.2 (B)
unnamed: OUT1.2, SW2A1.1 (A), SW2B1.3 (C)
unnamed: TONE1.1, VOL1.1
ON1: C3.2, C8.2, D5.1 (K), EYELED1.2 (A), F1.2, R2.2, SW2C1.3 (C), U1.8 (V+)
ON2: R4.1, SW2C1.2 (B)
OPAIn: R1.1, SW2A1.3 (C)
OPAOut: SW2B1.2 (B), VOL1.2
